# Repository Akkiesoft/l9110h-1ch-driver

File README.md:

# 1ch L9110H motor driver board

This is a 1-channel L9110H motor driver board. It is small and easy to solder.

## What you need besides this board

* 1x L9110H motor driver
* 2.54mm pin header
    * 1x 1x4
    * 1x 1x2
* 1x 0.1uf multilayer ceramic capacitor
* (Optional) 1x DIP-8 socket to make the L9110H interchangeable

## How to order boards using garber data

* zip garber-l9110h-1ch-driver-rev1 directory
* Upload zip to [JLCPCB](https://jlcpcb.com/) and order.

## Usage example

The following blogsa are written in Japanese, so please use a web translation services if necessary.

* https://akkiesoft.hatenablog.jp/entry/20230728/1690551535
* https://akkiesoft.hatenablog.jp/entry/20230802/1690982663

## License

MIT License

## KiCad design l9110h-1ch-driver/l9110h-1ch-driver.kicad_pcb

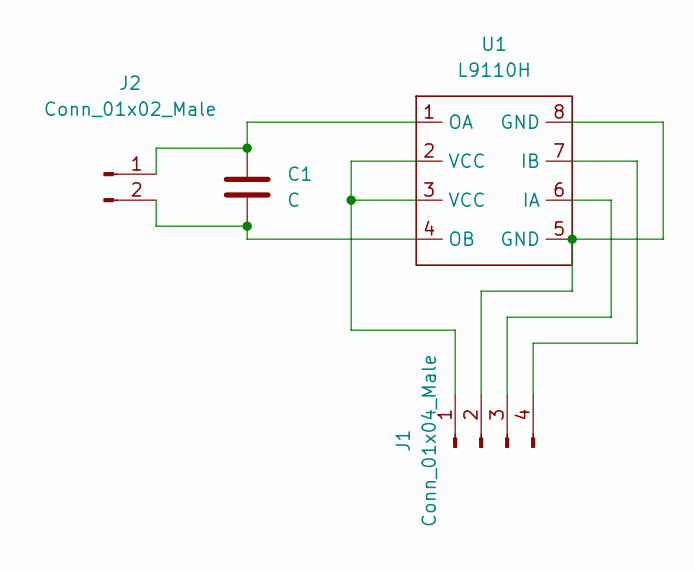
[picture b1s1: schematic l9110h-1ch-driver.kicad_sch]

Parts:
C1: C; C_Disc_D4.3mm_W1.9mm_P5.00mm
J1: Conn_01x04_Male; PinHeader_1x04_P2.54mm_Vertical
J2: Conn_01x02_Male; PinHeader_1x02_P2.54mm_Vertical
U1: L9110H; DIP-8_W7.62mm

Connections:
unnamed: C1.1, J2.1, U1.1 (OA)
unnamed: C1.2, J2.2, U1.4 (OB)
unnamed: J1.1, U1.2 (VCC), U1.3 (VCC)
unnamed: J1.2, U1.5 (GND), U1.8 (GND)
unnamed: J1.3, U1.6 (IA)
unnamed: J1.4, U1.7 (IB)

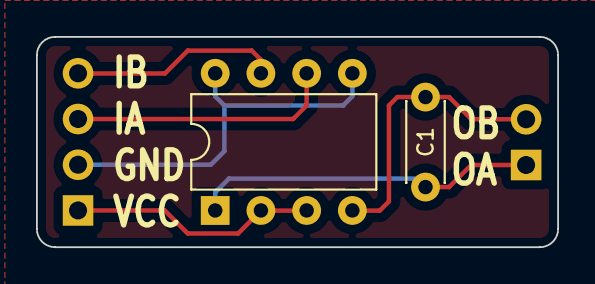
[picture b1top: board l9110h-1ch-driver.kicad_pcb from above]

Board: 2 copper layers, 29.0 x 11.7 mm, 4 parts (0 on the bottom side), 6 nets.

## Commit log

2023-07-17 nyan
